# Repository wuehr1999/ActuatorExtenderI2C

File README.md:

# ActuatorExtenderI2C
Control two DC motors and two Servos via I2C ( using an Arduino MKR )

## Features
* Connection header for Arduino MKR
* Qwiic connector
* Powertrain for two DC motors with back emf measurement, current sense, and emergency stop
* Connectors for 2 servo motors at 5V
* Car fuse
* Address selection jumpers

## Top Layer

## Bottom Layer

## References

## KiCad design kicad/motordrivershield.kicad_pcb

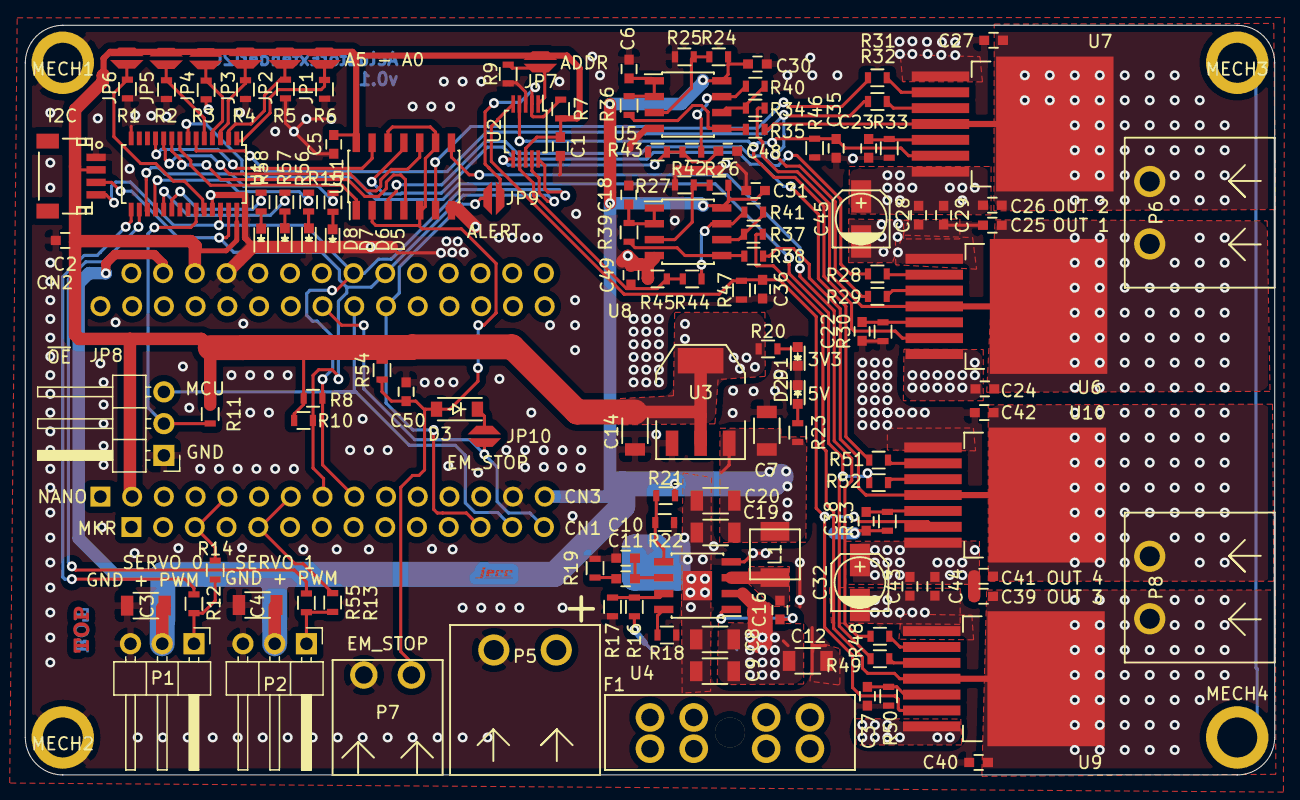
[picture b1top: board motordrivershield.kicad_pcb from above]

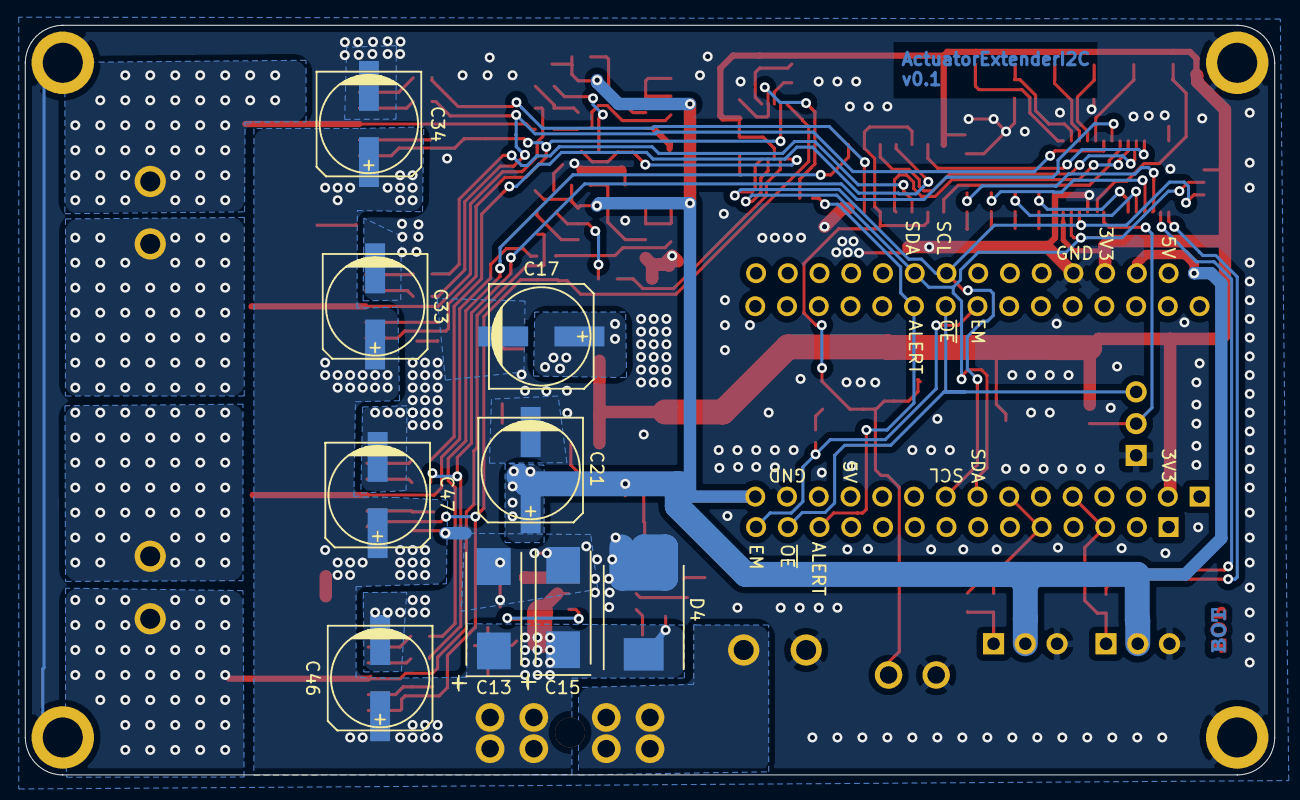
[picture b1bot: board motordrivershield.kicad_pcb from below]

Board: 2 copper layers, 100.0 x 60.0 mm, 155 parts (9 on the bottom side), 84 nets.

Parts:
C1, C2, C5, C6, C16, C18, C22, C23, C28, C29, C30, C31, C37, C38, C43, C44, C50: 100nF; C_0603
C3, C4, C14, C19, C20: 22uF; C_1206
C7: 10uF; C_1206
C8, C9: 4.7uF 50V; C_1206
C10: 120pF; C_0603
C11: 12nF; C_0603
C12: 100nF; C_1206
C13, C15: 47uF; TantalC_SizeD_EIA-7343_Wave
C17, C21: 47uF; c_elec_8x6.7
C24, C25, C26, C27, C39, C40, C41, C42: 220nF; C_0603
C32, C45: DNI; c_elec_4x4.5
C33, C34, C46, C47: DNI; c_elec_8x6.7
C35, C36, C48, C49: 1nF; C_0603
CN1: ARDUINO_MKR
CN2: QWIIC; Connectors_JST_SM04B-SRSS-TB
CN3: ARDUINO_NANO_33
D1, D2, D5, D6, D7, D8: Led_Small; LED_0603
D3: BAT46W; SOD-123
D4: D_Small; DO-214AB
F1: 15A; Fuseholder_ATO_Blade_littlefuse_8_Pin
JP1, JP2, JP3, JP4, JP5, JP6, JP7, JP9, JP10: Jumper_NO_Small; SolderJumper_2mm
JP8: JUMPER3; PinHeader_1x03_P2.54mm_Horizontal
L1: 74437324150; WE-LHMI40xx
L2: Label; jecc_logo
L3: Label; Top
L4: Label; Bot
MECH1, MECH2, MECH3, MECH4: MHP_3.2_5.0
P1, P2: CONN_01X03; PinHeader_1x03_P2.54mm_Horizontal
P5, P6, P8: WR-TBL_691313710002
P7: CONN_01X02; WR-TBL_691322310002
R1, R2, R3, R4, R5, R6, R7, R8, R9, R10, R11, R24, R26, R28, R29, R31, R32, R42, R44, R48, R49, R51, R52, R54: 10k; R_0603
R12, R13, R20, R23: 220; R_0603
R14, R55: 0R0; R_0603
R15, R46, R47, R56, R57, R58: 1k; R_0603
R16: 220k; R_0603
R17: 43.2k; R_0603
R18: 143k; R_0603
R19: 3.74k; R_0603
R21: 100k; R_0603
R22: 19.1k; R_0603
R25, R27: 5.6k; R_0603
R30, R33, R50, R53: 510; R_0603
R34, R35, R37, R38: 56k; R_0603
R36, R39, R40, R41, R43, R45: 22k; R_0603
U1: PCA9685_TSSOP28; TSSOP-28_4.4x9.7mm_Pitch0.65mm
U2: ADS1015; MSOP-10_3x3mm_Pitch0.5mm
U3: LT1117; SOT-223
U4: TPS54335A; SOIC-8-1EP_3.9x4.9mm_Pitch1.27mm
U5, U8: LM358; SOIC-8_3.9x4.9mm_Pitch1.27mm
U6, U7, U9, U10: IFX007T; TO-263-7Lead
U11: 74xx32; SOIC-14_3.9x8.7mm_Pitch1.27mm

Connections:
+3V3: C1.1, C2.1, C5.1, C14.1, C17.1, CN1.26, CN2.2, CN3.2, JP1.2, JP2.2, JP3.2, JP4.2, JP5.2, JP6.2, JP7.2, R7.2, R8.1, R10.1, R11.1, R20.1, R54.1, U1.28, U2.8, U3.2, U3.4, U11.14
+5V: C3.1, C4.1, C7.1, C19.1, C20.1, C21.1, C30.2, C31.2, CN1.27, CN3.15, L1.2, P1.2, P2.2, R21.1, R23.1, R24.1, R26.1, U3.3, U5.8, U8.8
+BATT: C8.1, C9.1, C12.1, C13.1, C15.1, C24.1, C26.1, C28.1, C29.1, C32.1, C33.1, C34.1, C39.1, C41.1, C43.1, C44.1, C45.1, C46.1, C47.1, D4.1, F1.2, R16.1, U4.2, U6.7, U7.7, U9.7, U10.7
/A0: JP1.1, R6.1, U1.1
/A1: JP2.1, R5.1, U1.2
/A2: JP3.1, R4.1, U1.3
/A3: JP4.1, R3.1, U1.4
/A4: JP5.1, R2.1, U1.5
/A5: JP6.1, R1.1, U1.24
/ADDR: JP7.1, R9.1, U2.1
/ALERT: JP9.2, R7.1, U2.2
/AL_MCU: CN1.12, CN3.21, JP9.1
/EM_MCU: CN1.14, CN3.23, JP10.1
/SCL: CN1.21, CN2.4, CN3.9, R8.2, U1.26, U2.10
/SDA: CN1.20, CN2.3, CN3.8, R10.2, U1.27, U2.9
/SERVO0_MCU: CN1.3, CN3.5, R14.2
/SERVO0_PCA: R12.2, U1.15
/SERVO1_MCU: CN1.5, CN3.7, R55.2
/SERVO1_PCA: R13.2, U1.16
/power/COMP: C10.1, C11.1, U4.6
/power/EN: R16.2, R17.1, U4.7
/power/PH: C16.1, L1.1, U4.3
/power/RT: R18.1, U4.8
/power/SENSE5V: R21.2, R22.1, U4.5
/powertrain/EM_S: C50.1, D3.2, P7.2, R54.2, U11.2, U11.5, U11.9, U11.12
/powertrain/IN1: R28.2, U11.3
/powertrain/IN2: R31.2, U11.6
/powertrain/IN3: R48.2, U11.8
/powertrain/IN4: R51.2, U11.11
/powertrain/OUT1: C24.2, C25.1, P6.1, R34.2, U6.4, U6.8
/powertrain/OUT2: C26.2, C27.1, P6.2, R35.2, U7.4, U7.8
/powertrain/OUT3: C39.2, C40.1, P8.1, R37.2, U9.4, U9.8
/powertrain/OUT4: C41.2, C42.1, P8.2, R38.2, U10.4, U10.8
/~OE: JP8.2, R11.2, U1.23
/~OE_MCU: CN1.13, CN3.22, JP8.3
BEMF12: C48.1, R42.2, R43.1, U2.6
BEMF34: C49.1, R44.2, R45.1, U2.7
EM_STOP: D3.1, JP10.2
GND: C1.2, C2.2, C3.2, C4.2, C5.2, C6.2, C7.2, C8.2, C9.2, C10.2, C12.2, C13.2, C14.2, C15.2, C17.2, C18.2, C19.2, C20.2, C21.2, C22.2, C23.2, C25.2, C27.2, C28.2, C29.2, C30.1, C31.1, C32.2, C33.2, C34.2, C35.2, C36.2, C37.2, C38.2, C40.2, C42.2, C43.2, C44.2, C45.2, C46.2, C47.2, C48.2, C49.2, C50.2, CN1.25, CN2.1, CN3.14, D1.1, D2.1, D4.2, D5.1, D6.1, D7.1, D8.1, JP8.1, MECH1.1, MECH2.1, MECH3.1, MECH4.1, P1.3, P2.3, P5.1, P7.1, R1.2, R2.2, R3.2, R4.2, R5.2, R6.2, R9.2, R17.2, R18.2, R19.2, R22.2, R25.2, R27.2, R30.2, R33.2, R43.2, R45.2, R46.2, R47.2, R50.2, R53.2, U1.14, U1.25, U2.3, U3.1, U4.4, U4.9, U5.4, U6.1, U7.1, U8.4, U9.1, U10.1, U11.7
INH12: R29.2, R32.2, U1.6
INH34: R49.2, R52.2, U1.7
IS12: C35.1, R46.1, U2.4, U6.6, U7.6
IS34: C36.1, R47.1, U2.5, U9.6, U10.6
unnamed: C6.1, R36.2, U5.1, U5.2
unnamed: C11.2, R19.1
unnamed: C16.2, U4.1
unnamed: C18.1, R39.2, U8.1, U8.2
unnamed: C22.1, R30.1, U6.5
unnamed: C23.1, R33.1, U7.5
unnamed: C37.1, R50.1, U9.5
unnamed: C38.1, R53.1, U10.5
unnamed: D1.2, R20.2
unnamed: D2.2, R23.2
unnamed: D5.2, R15.1
unnamed: D6.2, R56.1
unnamed: D7.2, R57.1
unnamed: D8.2, R58.1
unnamed: F1.1, P5.2
unnamed: P1.1, R12.1, R14.1
unnamed: P2.1, R13.1, R55.1
unnamed: R15.2, U1.17
unnamed: R24.2, R25.1, U5.3
unnamed: R26.2, R27.1, U8.3
unnamed: R28.1, U6.2
unnamed: R29.1, U6.3
unnamed: R31.1, U7.2
unnamed: R32.1, U7.3
unnamed: R34.1, R40.2, U5.6
unnamed: R35.1, R36.1, U5.5
unnamed: R37.1, R41.2, U8.6
unnamed: R38.1, R39.1, U8.5
unnamed: R40.1, R42.1, U5.7
unnamed: R41.1, R44.1, U8.7
unnamed: R48.1, U9.2
unnamed: R49.1, U9.3
unnamed: R51.1, U10.2
unnamed: R52.1, U10.3
unnamed: R56.2, U1.18
unnamed: R57.2, U1.19
unnamed: R58.2, U1.20
PWM1: U1.8, U11.1
PWM2: U1.9, U11.4
PWM3: U1.10, U11.10
PWM4: U1.11, U11.13

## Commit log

2020-09-15 added kicaddata and images
2020-09-16 ground improved
2020-09-16 rename
2020-09-17 added 5V to arduino header
2020-09-18 removed bak
2020-09-19 added reverse polarity and fixed emergency stop
2020-09-20 added nano footprint
2020-09-21 changed 5V power rail
2020-09-22 added capacitors
2020-09-26 added leds, updated capacitor values and changed silkscreen
2020-09-26 added ibom page
2020-09-26 updated docs
2020-09-26 bom update
2020-09-27 improved emergency stop for breaking
2020-09-27 improved emergency stop circuit for breaking
2020-10-03 layout improvement
2020-10-10 improved ifx ground
2020-11-14 swapped sda and scl on pca9685
2020-11-20 blöden servo wegen kompass gemacht
2020-11-21 added ruleset tex file
2020-11-22 servos angepasst
2020-11-22 blöder servo
2021-12-26 .github folder
2021-12-26 workflows
2021-12-26 new workflow
2021-12-26 rm kicad folder
2021-12-26 added schs
2021-12-26 mv files
2021-12-26 rm docs
2021-12-26 netlist
2021-12-26 docs
